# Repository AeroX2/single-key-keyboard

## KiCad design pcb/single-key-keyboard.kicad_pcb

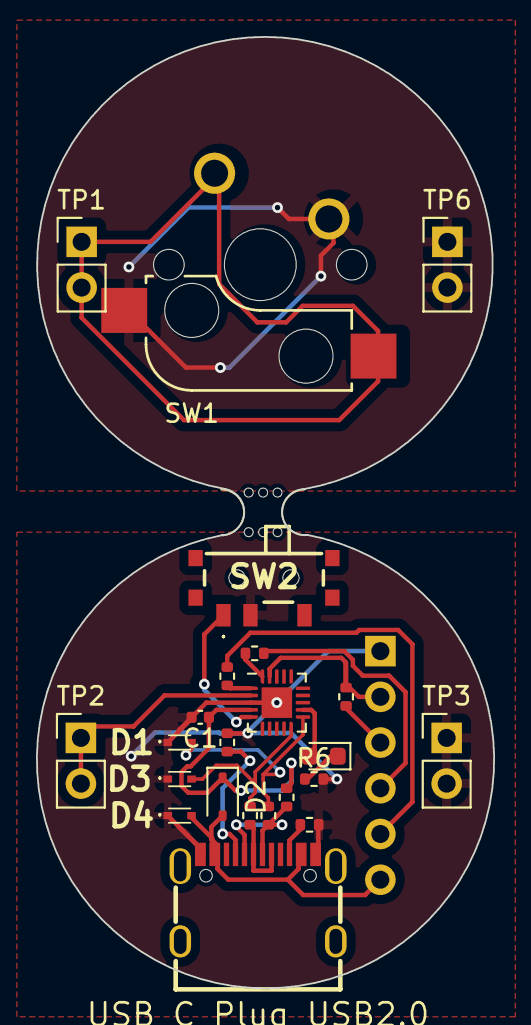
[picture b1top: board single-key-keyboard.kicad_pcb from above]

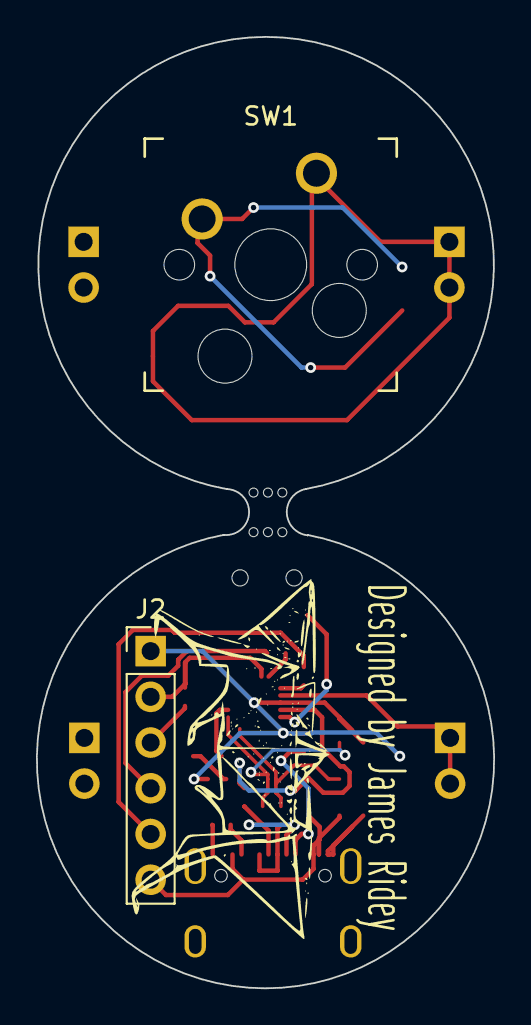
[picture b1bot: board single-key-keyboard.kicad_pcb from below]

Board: 2 copper layers, 25.4 x 52.9 mm, 25 parts (2 on the bottom side), 21 nets.

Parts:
C1: 100n; C_0402_1005Metric
D1, D3, D4: LESD5D5.0CT1G; LESD5D50CT1G
D2: D_Schottky; D_SOD-323
D5: LED; LED_0603_1608Metric
H2: MountingHole; mouse-bite-2.54mm-slot
J2: Conn_01x05; PinHeader_1x06_P2.54mm_Vertical
P1: USB_C_Plug_USB2.0; USB-C-SMD_KH-TYPE-C-16P
R1, R2: 5.1k; R_0402_1005Metric
R3, R4: 1k; R_0402_1005Metric
R5: 4.7k; R_0402_1005Metric
R6: 500; R_0402_1005Metric
R7: 1.5k; R_0402_1005Metric
R8, R9: 68; R_0402_1005Metric
SW1: SW_Push; Kailh_socket_MX_optional
SW2: SW_SPST; TA3524AA
TP1, TP2, TP3, TP6: TestPoint; PinHeader_1x02_P2.54mm_Vertical
U1: ATtiny416-M; VQFN-20-1EP_3x3mm_P0.4mm_EP1.7x1.7mm

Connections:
+5VP: C1.1, D2.1 (K), R7.1, U1.4 (VCC)
/D+: D3.2, R9.2, U1.10 (PB4)
/D-: D1.2, R8.2, U1.11 (PB3)
/PA0 UPDI: J2.2, R5.1, U1.19 (~RESET/PA0)
/PA1 UART TX: R3.1, U1.20 (PA1)
/PA2 UART RX: R4.1, U1.1 (PA2)
/PA3: TP2.1, TP2.2, U1.2 (PA3)
/PA4: SW2.1 (A), U1.5 (PA4)
/PB2: D5.2 (A), U1.12 (PB2)
/VIN: D2.2 (A), D4.2, J2.6, P1.A4 (VBUS), P1.A9 (VBUS), P1.B4 (VBUS), P1.B9 (VBUS)
GND: C1.2, D1.1, D3.1, D4.1, J2.1, P1.A1 (GND), P1.A12 (GND), P1.B1 (GND), P1.B12 (GND), R1.1, R2.1, R6.2, SW2.2 (B), TP3.1, TP3.2, U1.3 (GND), U1.21 (GND)
GND2: SW1.2, TP6.1, TP6.2
unnamed: D5.1 (K), R6.1
unnamed: J2.3, R5.2
unnamed: J2.4, R3.2
unnamed: J2.5, R4.2
unnamed: P1.A5 (CC1), R2.2
unnamed: P1.B5 (CC2), R1.2
unnamed: P1.A6 (D+), P1.B6 (D+), R9.1
unnamed: P1.A7 (D-), P1.B7 (D-), R7.2, R8.1
unnamed: SW1.1, TP1.1, TP1.2

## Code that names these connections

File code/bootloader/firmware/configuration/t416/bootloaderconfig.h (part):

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 *
 * Controller type: ATtiny 416 - 16.5 MHz
 * Configuration:   Default configuration
 *       USB D- :   PB3
 *       USB D+ :   PB4
 *       Entry  :   Always
 *       LED    :   None
 *       OSCCAL :   Stays at 16 MHz
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 *
 */

#define JUMPER_PIN    PA1
#define JUMPER_PORT   PORTA
#define JUMPER_DDR    DDRA
#define JUMPER_INP    PINA
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
#define LED_DDR     DDRB
#define LED_PORT    PORTB
#define LED_PIN     PB2

/*
 *  This is the implementation of the LED code. Change the configuration above unless you want to
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
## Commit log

2023-08-06 Second commit
2023-08-06 Add logo
2023-08-23 Move files to PCB folder, add new code folder
2023-08-23 Start adding bootloader code
2023-08-24 Remove panel stuff
2023-08-24 Change bootloader to megaTinyCore instead
2023-08-24 Use the tinyAVR1 V-USB code
2023-08-24 Code compiles and pick correct pcb version
2023-08-25 Finally got the keyboard part working
2023-08-25 Attempt 1 at combining a USBKeyboard and USBSerial device
2023-08-28 Remove files that don't need to be committed
2023-08-28 Second attempt to combine Keyboard and Serial
2023-08-30 It finally works on both Linux and Windows
2023-09-01 Attempt to use raw C rather than Arduino
2023-09-14 Transistion over to native instead of Arduino framework
2023-09-20 temporary commit
2023-09-21 Hopefully final version of code, support new strings and EEPROM
2023-09-23 Get away with a slightly longer keyboard string
2023-11-10 Wrong library name :(

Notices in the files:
code/bootloader/firmware/configuration/t416/bootloaderconfig.h:
License: GNU GPL v2 (see License.txt
